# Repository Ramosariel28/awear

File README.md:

# AWear

* **Tagline:** Awareness you can wear because we care
* **Purpose:** Medical Dashboard; Partnered with a Wireless Biometric Bracelet
* **Framework:** Flutter
* **Platform:** Desktop (Windows) and Mobile (Android)

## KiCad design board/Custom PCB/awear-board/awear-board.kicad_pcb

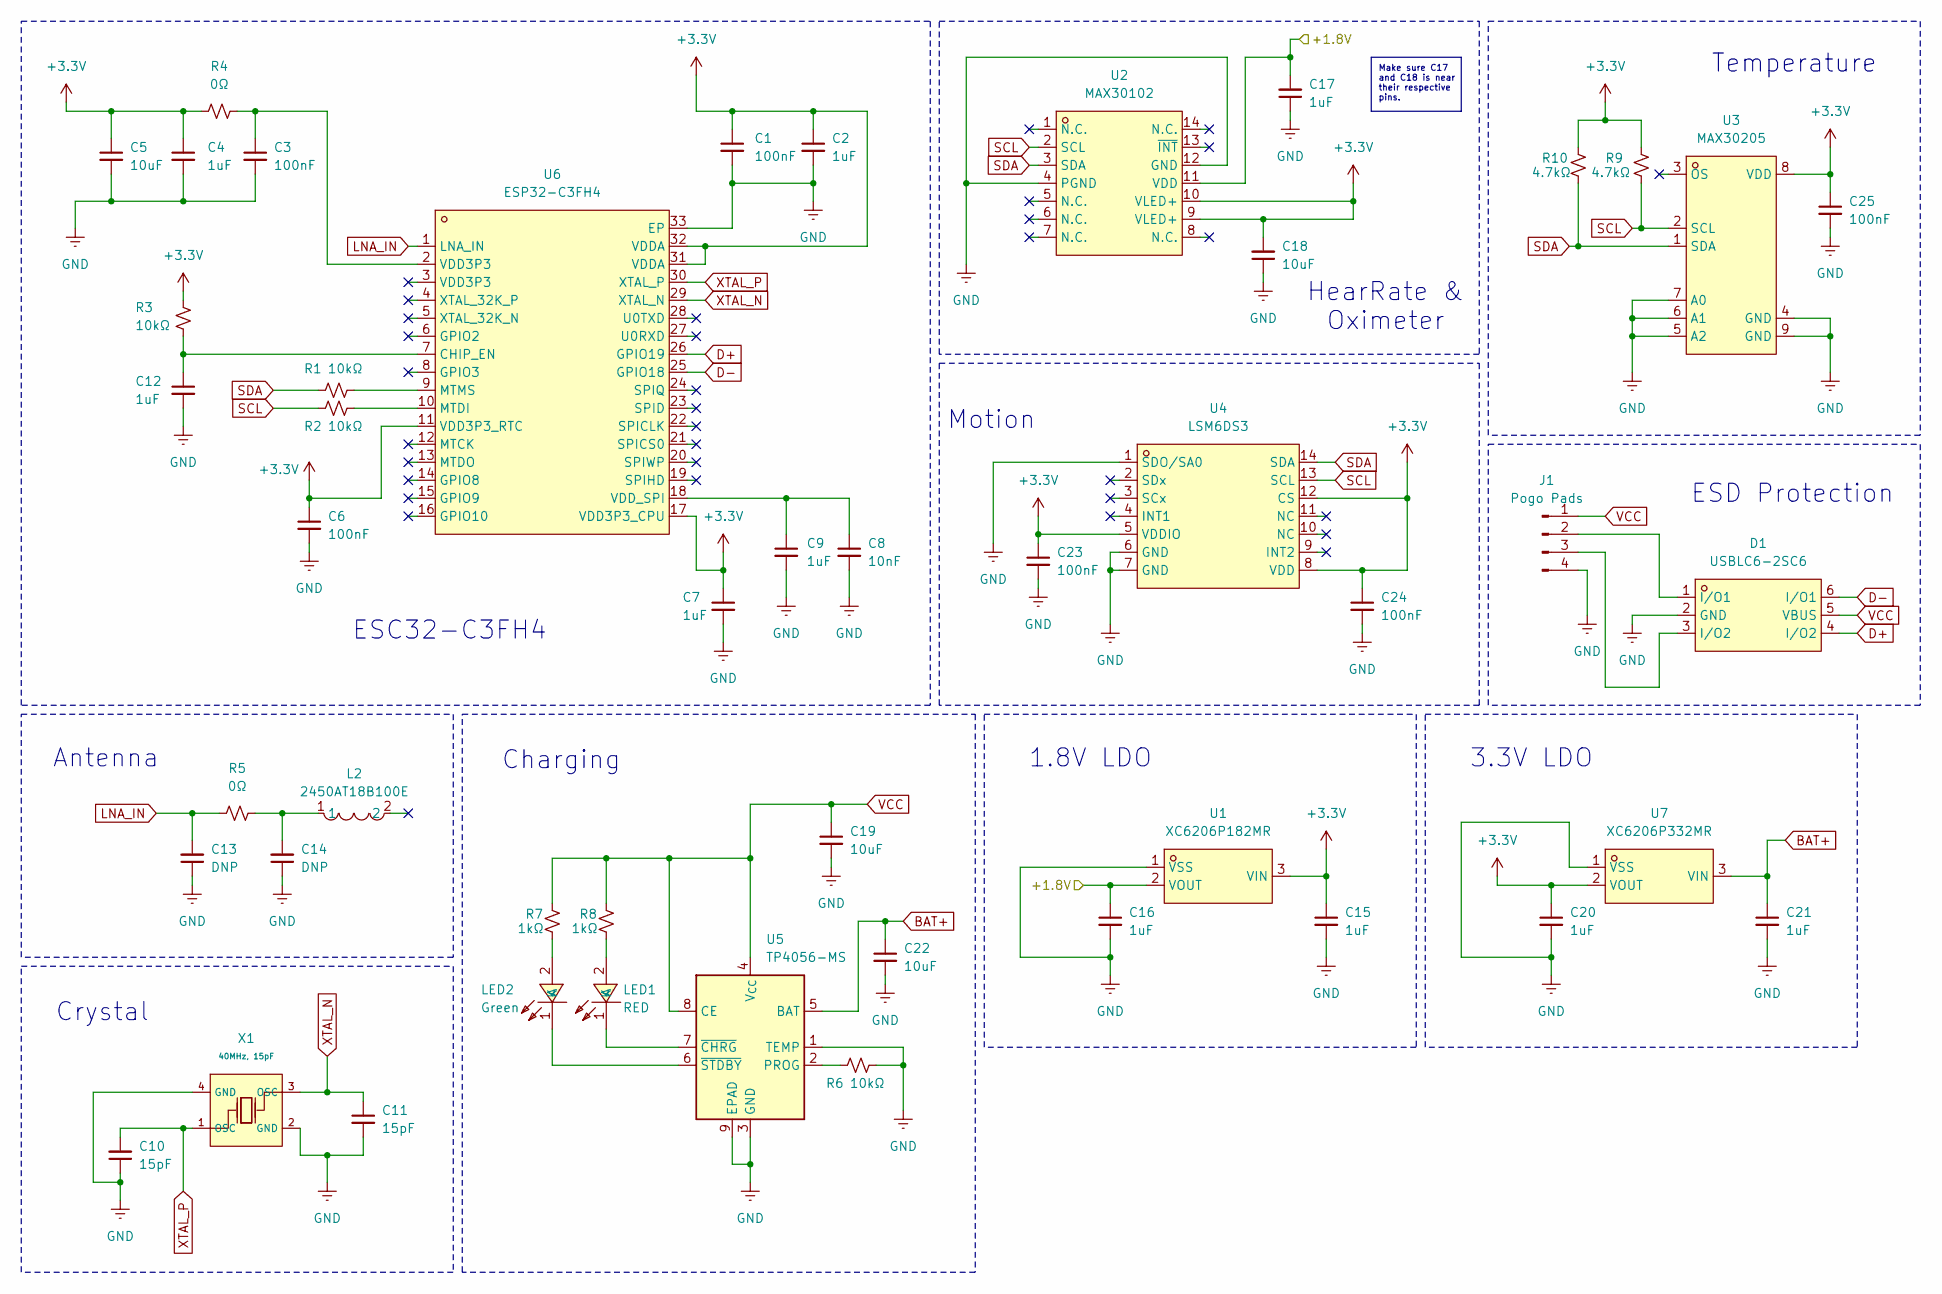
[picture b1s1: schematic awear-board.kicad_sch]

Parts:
C1, C3, C6, C23, C24, C25: 100nF; C_0201_0603Metric
C2, C4, C7, C9, C12, C15, C16, C17, C20, C21: 1uF; C_0402_1005Metric
C5, C22: 10uF; C_01005_0402Metric
C8: 10nF; C_0201_0603Metric
C10, C11: 15pF; C_0201_0603Metric
C13, C14: DNP; C_0201_0603Metric
C18, C19: 10uF; C_0402_1005Metric
D1: USBLC6-2SC6; SOT-23-6_L2.9-W1.6-P0.95-LS2.8-BL; LCSC Part C2687116
J1: Pogo Pads; PogoPad
L2: 2450AT18B100E; ANT-SMD_L3.2-W1.6; LCSC Part C2917717
LED1: RED; LED0603-RD; LCSC Part C2286
LED2: Green; LED0603-RD; LCSC Part C2289
R1, R2, R3, R6: 10kΩ; R_0201_0603Metric
R4, R5: 0Ω; R_0201_0603Metric
R7, R8: 1kΩ; R_0201_0603Metric
R9, R10: 4.7kΩ; R_0201_0603Metric
U1: XC6206P182MR; SOT-23-3_L3.0-W1.7-P0.95-LS2.9-BR; LCSC Part C347373
U2: MAX30102; OESIP-14_L5.6-W3.3-P0.80-TL; LCSC Part C6454833
U3: MAX30205; TDFN-8_L3.0-W3.0-P0.65-BL-EP2.3; LCSC Part C476171
U4: LSM6DS3; LGA-14_L3.0-W2.5-P0.50-TL; LCSC Part C967633
U5: TP4056-MS; SOIC-8-1EP_3.9x4.9mm_P1.27mm_EP2.41x3.3mm_ThermalVias
U6: ESP32-C3FH4; QFN-32_L5.0-W5.0-P0.50-TL-EP3.7; LCSC Part C2858491
U7: XC6206P332MR; SOT-23-3_L3.0-W1.7-P0.95-LS2.9-BR; LCSC Part C347376
X1: 40MHz, 15pF; OSC-SMD_4P-L3.2-W2.5-BL_SIT8008BI; PartID X322540MPB4SI; LCSC C9010

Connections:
+3.3V: C1.1, C2.1, C4.1, C5.1, C6.1, C7.1, C15.1, C18.2, C20.1, C23.1, C24.1, C25.1, R3.2, R4.2, R9.1, R10.1, U1.3 (VIN), U2.9 (VLED+), U2.10 (VLED+), U3.8 (VDD), U4.5 (VDDIO), U4.8 (VDD), U4.12 (CS), U6.11 (VDD3P3_RTC), U6.17 (VDD3P3_CPU), U6.31 (VDDA), U6.32 (VDDA), U7.2 (VOUT); also elsewhere on the board
/+1.8V: C16.1, C17.2, U1.2 (VOUT), U2.11 (VDD)
BAT+: C21.1, C22.1, U5.5 (BAT), U7.3 (VIN)
D+: D1.4 (I/O2), U6.26 (GPIO19)
D-: D1.6 (I/O1), U6.25 (GPIO18)
GND: C1.2, C2.2, C3.2, C4.2, C5.2, C6.2, C7.2, C8.2, C9.2, C10.1, C11.2, C12.2, C13.1, C14.1, C15.2, C16.2, C17.1, C18.1, C19.2, C20.2, C21.2, C22.2, C23.2, C24.2, C25.2, D1.2 (GND), J1.4, R6.2, U1.1 (VSS), U2.4 (PGND), U2.12 (GND), U3.4 (GND), U3.5 (A2), U3.6 (A1), U3.7 (A0), U3.9 (GND), U4.1 (SDO/SA0), U4.6 (GND), U4.7 (GND), U5.1 (TEMP), U5.3 (GND), U5.9 (EPAD), U6.33 (EP), U7.1 (VSS), X1.2 (GND), X1.4 (GND)
LNA_IN: C13.2, R5.2, U6.1 (LNA_IN)
unnamed 7: C3.1, R4.1, U6.2 (VDD3P3); also elsewhere on the board
unnamed: C14.2, L2.1, R5.1
unnamed: D1.1 (I/O1), J1.2
unnamed: D1.3 (I/O2), J1.3
unnamed: LED1.2 (A), R8.2
unnamed: LED1.1 (K), U5.7 (~CHRG)
unnamed: LED2.2 (A), R7.2
unnamed: LED2.1 (K), U5.6 (~STDBY)
unnamed: R6.1, U5.2 (PROG)
unnamed: C12.1, R3.1, U6.7 (CHIP_EN)
unnamed: R2.2, U6.10 (MTDI)
unnamed: R1.1, U6.9 (MTMS)
unnamed: C8.1, C9.1, U6.18 (VDD_SPI)
SCL: R2.1, R9.2, U2.2 (SCL), U3.2 (SCL), U4.13 (SCL)
SDA: R1.2, R10.2, U2.3 (SDA), U3.1 (SDA), U4.14 (SDA)
VCC: C19.1, D1.5 (VBUS), J1.1, R7.1, R8.1, U5.4 (V_{CC}), U5.8 (CE)
XTAL_N: C11.1, U6.29 (XTAL_N), X1.3 (OSC)
XTAL_P: C10.2, U6.30 (XTAL_P), X1.1 (OSC)

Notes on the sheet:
1.8V LDO
Temperature
Antenna
Crystal
ESC32-C3FH4
HearRate & Oximeter
ESD Protection
3.3V LDO
Motion
Charging
Make sure C17 and C18 is near their respective pins.

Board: 2 copper layers, 49 parts (0 on the bottom side), 25 nets, no tracks yet.

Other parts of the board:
L1: 1uH,50mA; L_0805

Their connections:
+3.3V: L1.1; also elsewhere on the board
unnamed 7: L1.2; also elsewhere on the board

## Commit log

2026-01-07 Just updating README
2026-01-07 Fix readme formatting
2026-01-08 Unreliably but was able to detect sender device now.
2026-01-08 Updated sender device persistency and the pair user action
2026-01-08 At least plugs in and out much better
2026-01-08 Made the receiver much more reliable, gets recognized even if already connected.
2026-01-12 New Splash Screen
2026-01-12 Fixes User-Device Pairing UI Update
2026-01-12 Fixes User receiving sensor data
2026-01-16 Added Board Designs
2026-01-20 Fixes Saving to Database
2026-01-20 Fixes Sender Device Pairing
2026-01-20 Updated to version 0.8.0
2026-01-20 Fixed Serial Port not Closing
2026-01-22 Finished Mobile Application and Notification System
2026-01-22 sum update
2026-01-22 Added About Button, Updated Logo, Fixed User Registration, CleanUp
2026-01-22 For Release; Comment Out Prints
2026-01-28 Update to 1.0.1; More Sections
